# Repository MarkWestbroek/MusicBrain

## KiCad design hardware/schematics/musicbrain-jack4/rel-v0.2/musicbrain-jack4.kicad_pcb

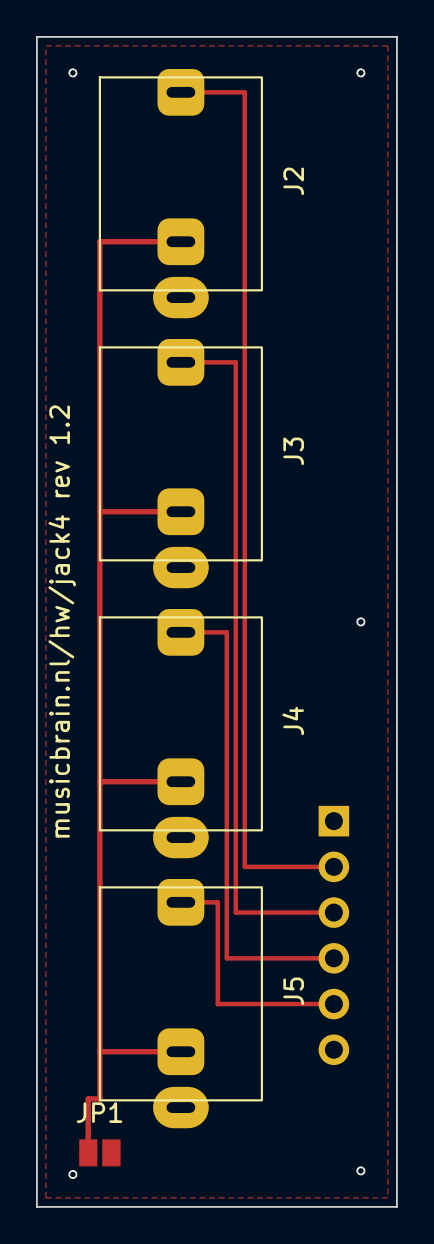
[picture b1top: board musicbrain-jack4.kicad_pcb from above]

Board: 2 copper layers, 20.0 x 65.0 mm, 6 parts (1 on the bottom side), 6 nets.

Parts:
J1: SOCKET-BACK; Header_1x06_backside
J2, J3, J4, J5: PJ398SM; Jack_3.5mm_PJ398SM_Thonkiconn
JP1: NORM=GND; SolderJumper-2_P1.3mm_Open_TrianglePad1.0x1.5mm

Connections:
/CH1: J1.2, J2.1
/CH2: J1.3, J3.1
/CH3: J1.4, J4.1
/CH4: J1.5, J5.1
/NORM: J2.3, J3.3, J4.3, J5.3, JP1.1
GND: J1.1, J1.6, J2.2, J3.2, J4.2, J5.2, JP1.2

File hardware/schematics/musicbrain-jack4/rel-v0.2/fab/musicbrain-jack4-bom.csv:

"Comment","Designator","Footprint","LCSC Part #"
"NAAR KAART","J1","PinSocket_1x06_P2.54mm_Vertical",""
"PJ398SM","J2,J3,J4,J5","Jack_3.5mm_PJ398SM_Thonkiconn",""
"NORM=GND (dicht voor inputs)","JP1","SolderJumper-2_P1.3mm_Open_TrianglePad1.0x1.5mm",""

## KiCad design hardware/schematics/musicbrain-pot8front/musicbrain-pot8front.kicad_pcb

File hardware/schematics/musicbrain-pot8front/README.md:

# MusicBrain POT8-FRONT — dom front, 8× RK097N verticaal

**Praktisch:** acht potmeters aan het paneel op één strak
13,75mm-raster; samen met de potriser worden het acht vrij toewijsbare
stuurspanningen.

**Status**: rev 1.1 — ERC 0, netlijst pad-voor-pad geverifieerd, DRC 0/0. Bord 20×110 mm, 2 lagen.
**Model**: route 2 (2026-07-11): plat front-bord aan het paneel; elektronica zit
op de riser/kaart eronder. Dit bord is puur passief.

**v1.1 (2026-07-11)**: 3D-model van de socket staat nu óp de gatenrij
(canonieke geflipte footprint-vorm); silk-URL naar bordmidden (viel over de
rand); PCB-papier A3. Koper identiek aan v1.0.

## Geometrie (de front-standaard)

- **As-hartlijn = 8,0 mm van de westrand** — zelfde lijn als de Thonkiconns op
  jack8/jack4, zodat het paneel overal hetzelfde ritme heeft.
- 8× RK097N (9 mm, verticaal, M7-bus + moer) op **13,75 mm steek** (110/8).
- **J1 = 1×10 female socket op de ACHTERZIJDE** in de ooststrook (x 16,5),
  gecentreerd op halve bordhoogte. Contract: **1 = GND, 2..9 = W1..W8, 10 = +3V3**.
- Beugelsleuven zijn koperloos (NPTH): het front hangt aan de M7-moeren.

## ⚠️ Vóór paneel-fab: SHAFT_OFFSET meten

De footprint ankert op het **as-hart**; de pinnenrij ligt op `SHAFT_OFFSET` =
**4,5 mm** (aanname uit de datasheettekening: 6,5 − 2,0). **Meet dit aan een
fysieke pot** (afstand hart pinnenrij → hart as). Wijkt het af: pas
`SHAFT_OFFSET` in `hardware/kicad-generators/gen_pot8front.py` aan en
regenereer — de as-hartlijn (8,0) blijft dan kloppen.

## Elektrisch

Pin 3 (CW-eind) → +3V3, pin 1 (CCW) → GND, pin 2 (loper) → W-k: rechtsom
draaien = hogere spanning = hogere ADC-waarde. De MCP3208 zit op de pot-riser
(of gebruik de bestaande `musicbrain-pot8`-kaart als drager); 100 nF-reservoirs
per loper zitten dáár, niet op dit front.

## Aansluitoverzicht

### Pinouts

Bovenaanzicht van het bord (kijkend op de pinnen); pin 1 = vierkant. Gegenereerd uit het bordbestand met `hardware/kicad-generators/pinout_svg.py`.

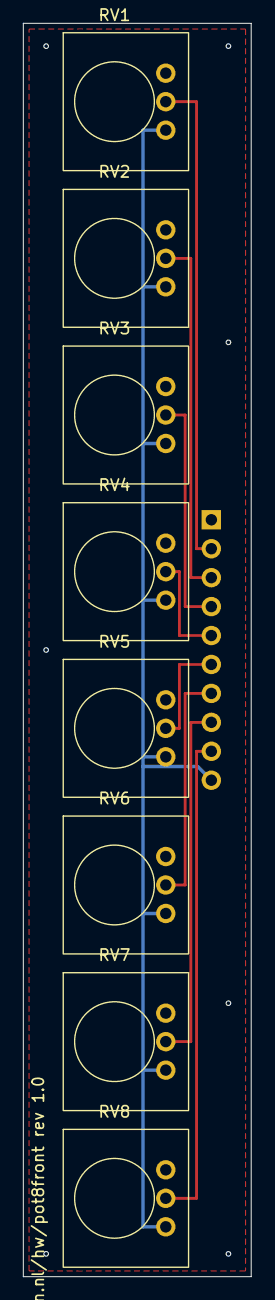
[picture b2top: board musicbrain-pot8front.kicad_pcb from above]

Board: 2 copper layers, 20.0 x 110.0 mm, 9 parts (1 on the bottom side), 10 nets.

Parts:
J1: SOCKET-BACK; Socket_1x10_backside
RV1, RV2, RV3, RV4, RV5, RV6, RV7, RV8: RK097N 10k; RK097N_Vertical

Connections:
+3V3: J1.10, RV1.3, RV2.3, RV3.3, RV4.3, RV5.3, RV6.3, RV7.3, RV8.3
/W1: J1.2, RV1.2
/W2: J1.3, RV2.2
/W3: J1.4, RV3.2
/W4: J1.5, RV4.2
/W5: J1.6, RV5.2
/W6: J1.7, RV6.2
/W7: J1.8, RV7.2
/W8: J1.9, RV8.2
GND: J1.1, RV1.1, RV2.1, RV3.1, RV4.1, RV5.1, RV6.1, RV7.1, RV8.1

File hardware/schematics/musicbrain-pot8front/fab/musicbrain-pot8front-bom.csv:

"Comment","Designator","Footprint","LCSC Part #"
"NAAR RISER (achterzijde)","J1","Socket_1x10_backside",""
"RK097N 10k lin","RV1,RV2,RV3,RV4,RV5,RV6,RV7,RV8","RK097N_Vertical",""

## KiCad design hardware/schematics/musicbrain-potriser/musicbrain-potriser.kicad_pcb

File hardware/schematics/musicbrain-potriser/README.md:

# MusicBrain POT-RISER — MCP3208-riser voor het POT8-FRONT

**Praktisch:** maakt van acht paneelpotmeters CV-bronnen: staat in een
slot, leest het pot8front uit en zet alle acht waardes op de bus.

**Status**: rev 2.0 — ERC 0, netlijst pad-voor-pad geverifieerd, DRC 0/0.
Bord **40 × 45 mm**, 2 lagen.

## Gen 2 (rev 2.0, 2026-07-16)

- Slot **2×12**; H 80 → 45; bord 28 → 40 breed.
- MCP3208 gedraaid: kanalen noordwaarts naar de reservoirs, SPI+GND
  zuidwaarts (anders raakte AGND opgesloten van het vlak).
- Koper via freerouting (SES naast het bord).

De schakelingbeschrijving hieronder is ongewijzigd; waar de lopende
tekst nog gen-1-maten of 2×10 noemt, geldt bovenstaande. Overzicht en
pinouts hieronder zijn gen-2-gegenereerd.
**Model**: route 2 — het domme POT8-FRONT ligt plat aan het paneel; deze smalle
riser staat eronder in het busboard-slot en draagt de elektronica.

## Connectoren

- **J1** (haakse male 2×10, onderrand): het busboard-slot in. Gebruikt alleen
  GND / +3V3 / SCLK / MOSI / MISO / CS; de rest (±12V, LDAC, IRQ, I2C, SPARE)
  is onaangesloten.
- **J2** (haakse male 1×10, bovenrand): het POT8-FRONT in.
  **Contract: 1 = GND, 2..9 = W1..W8 (lopers), 10 = +3V3.**
  ⚠️ Pin-1-oriëntatie t.o.v. de front-socket bij de eerste passing verifiëren
  (front-socket zit op de achterzijde); klopt de volgorde niet, dan de
  J2-map in `gen_potriser.py` spiegelen en regenereren.

## Elektrisch

- MCP3208 (SOIC-16), SPI mode 0, ratiometrisch (VREF = VDD = +3V3).
- CH0..CH7 = W1..W8 = paneel boven→onder.
- 100 nF-laadreservoir per loper (C1–C8) direct achter J2, 100 nF ontkoppeling (C9).
- Firmware: bestaande `MbPot8`-driver werkt ongewijzigd (zelfde chip + mapping).

## Waarom dit bord

De pot8-slotkaart (110×80, met haakse pots erop) is geen drager voor het
front-model: pots zitten in de weg, geen frontconnector en onnodig breed
(besluit 2026-07-11). Deze riser vervangt hem in het pot-spoor; de pot8-kaart
blijft bruikbaar als losstaand alternatief zonder front.

## Aansluitoverzicht

### Pinouts

Bovenaanzicht van het bord (kijkend op de pinnen); pin 1 = vierkant. Gegenereerd uit het bordbestand met `hardware/kicad-generators/pinout_svg.py`.

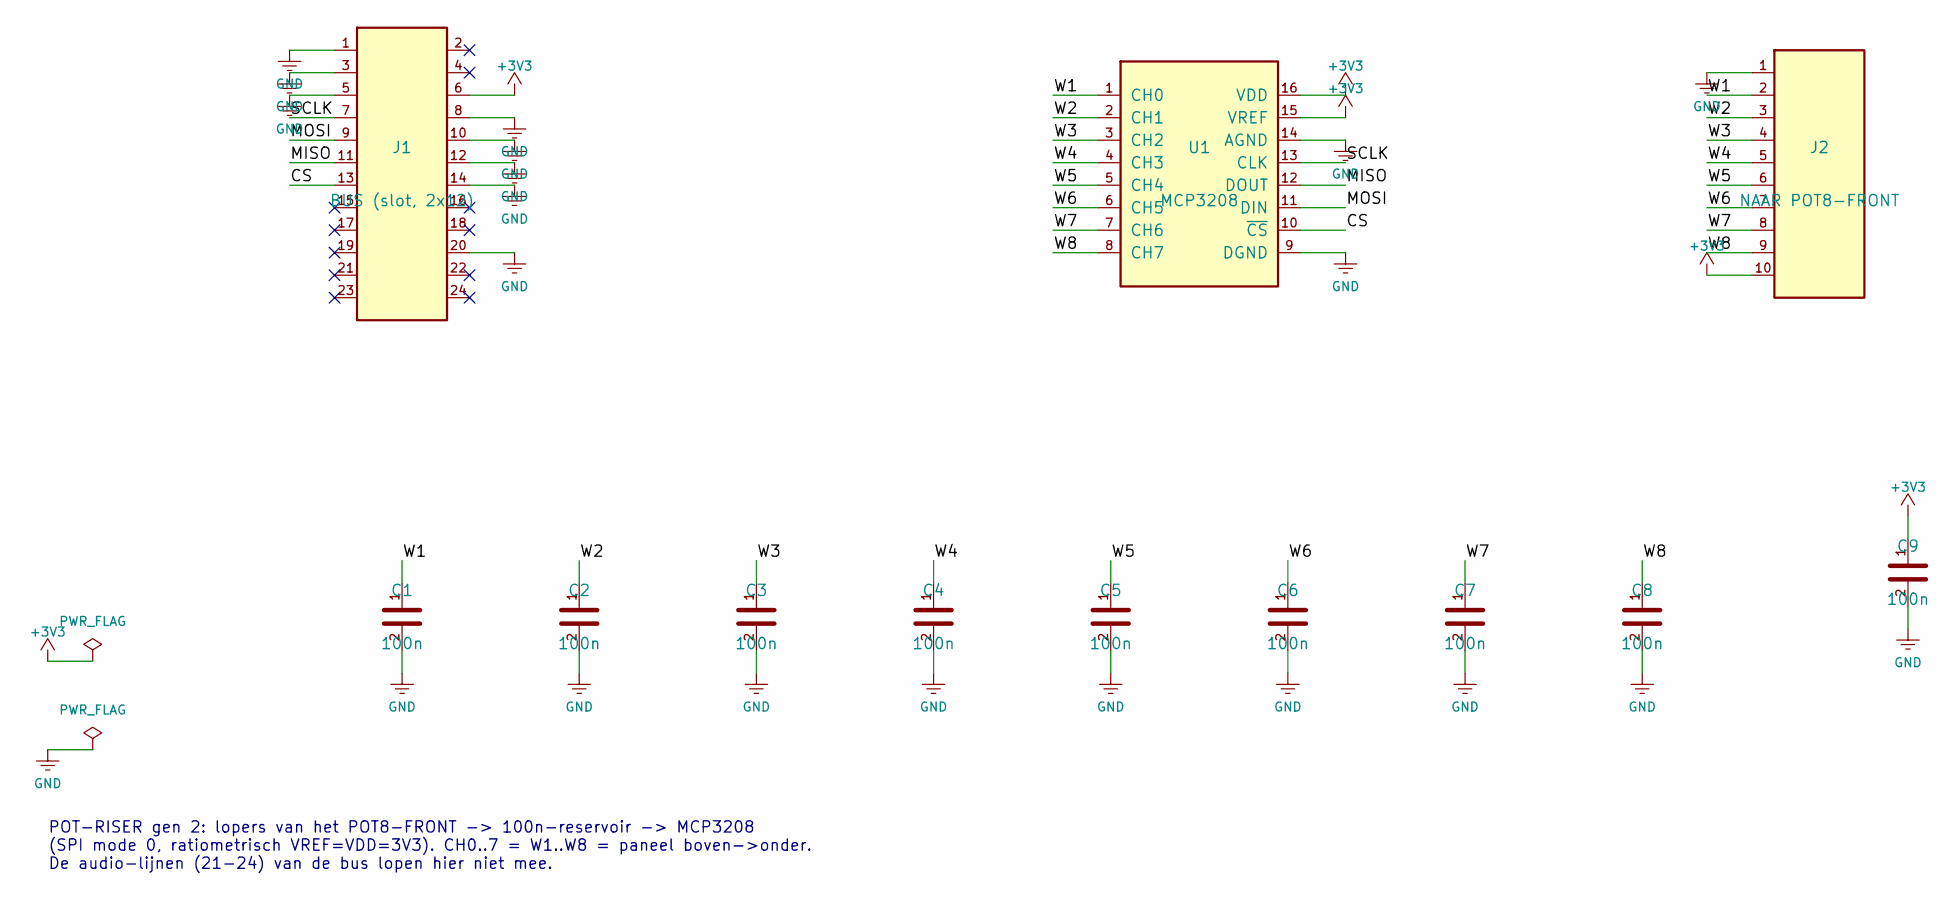
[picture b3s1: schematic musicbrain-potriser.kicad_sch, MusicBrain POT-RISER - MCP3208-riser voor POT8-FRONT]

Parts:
C1, C2, C3, C4, C5, C6, C7, C8, C9: 100n; C_0805_2012Metric
J1: BUS (slot, 2x12); PinHeader_2x12_P2.54mm_Horizontal
J2: NAAR POT8-FRONT; PinHeader_1x10_P2.54mm_Horizontal
U1: MCP3208; SOIC-16_3.9x9.9mm_P1.27mm

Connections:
+3V3: C9.1, J1.6, J2.10, U1.15 (VREF), U1.16 (VDD)
/CS: J1.13, U1.10 (~CS)
/MISO: J1.11, U1.12 (DOUT)
/MOSI: J1.9, U1.11 (DIN)
/SCLK: J1.7, U1.13 (CLK)
/W1: C1.1, J2.2, U1.1 (CH0)
/W2: C2.1, J2.3, U1.2 (CH1)
/W3: C3.1, J2.4, U1.3 (CH2)
/W4: C4.1, J2.5, U1.4 (CH3)
/W5: C5.1, J2.6, U1.5 (CH4)
/W6: C6.1, J2.7, U1.6 (CH5)
/W7: C7.1, J2.8, U1.7 (CH6)
/W8: C8.1, J2.9, U1.8 (CH7)
GND: C1.2, C2.2, C3.2, C4.2, C5.2, C6.2, C7.2, C8.2, C9.2, J1.1, J1.3, J1.5, J1.8, J1.10, J1.12, J1.14, J1.20, J2.1, U1.9 (DGND), U1.14 (AGND)

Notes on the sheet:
POT-RISER gen 2: lopers van het POT8-FRONT -> 100n-reservoir -> MCP3208 (SPI mode 0, ratiometrisch VREF=VDD=3V3). CH0..7 = W1..W8 = paneel boven->onder. De audio-lijnen (21-24) van de bus lopen hier niet mee.

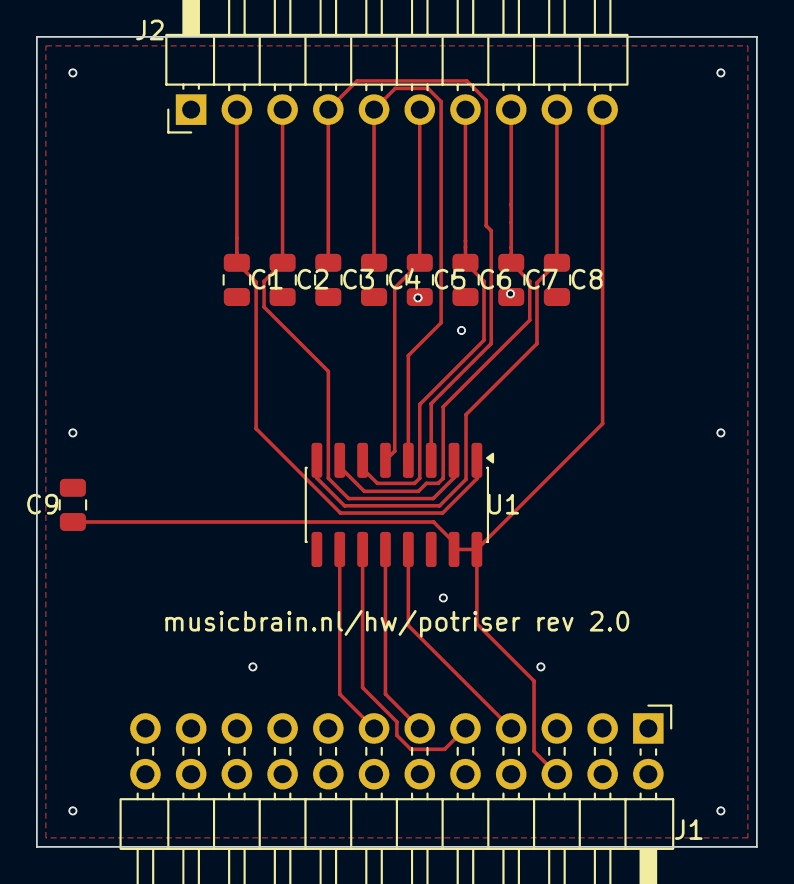
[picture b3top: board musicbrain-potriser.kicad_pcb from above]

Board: 2 copper layers, 40.0 x 45.0 mm, 12 parts (0 on the bottom side), 14 nets.

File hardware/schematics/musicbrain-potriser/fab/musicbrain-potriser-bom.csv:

"Comment","Designator","Footprint","LCSC Part #"
"100n","C1,C2,C3,C4,C5,C6,C7,C8,C9","C_0805_2012Metric","C49678"
"BUS","J1","PinHeader_2x10_P2.54mm_Horizontal",""
"NAAR POT8-FRONT","J2","PinHeader_1x10_P2.54mm_Horizontal",""
"MCP3208","U1","SOIC-16_3.9x9.9mm_P1.27mm","C16939"
